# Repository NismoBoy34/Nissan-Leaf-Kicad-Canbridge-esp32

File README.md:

# Nissan-Leaf-Kicad-Canbridge-esp32
Esp32 based Can-bridge for the Nissan leaf / Env200 using more accessible components

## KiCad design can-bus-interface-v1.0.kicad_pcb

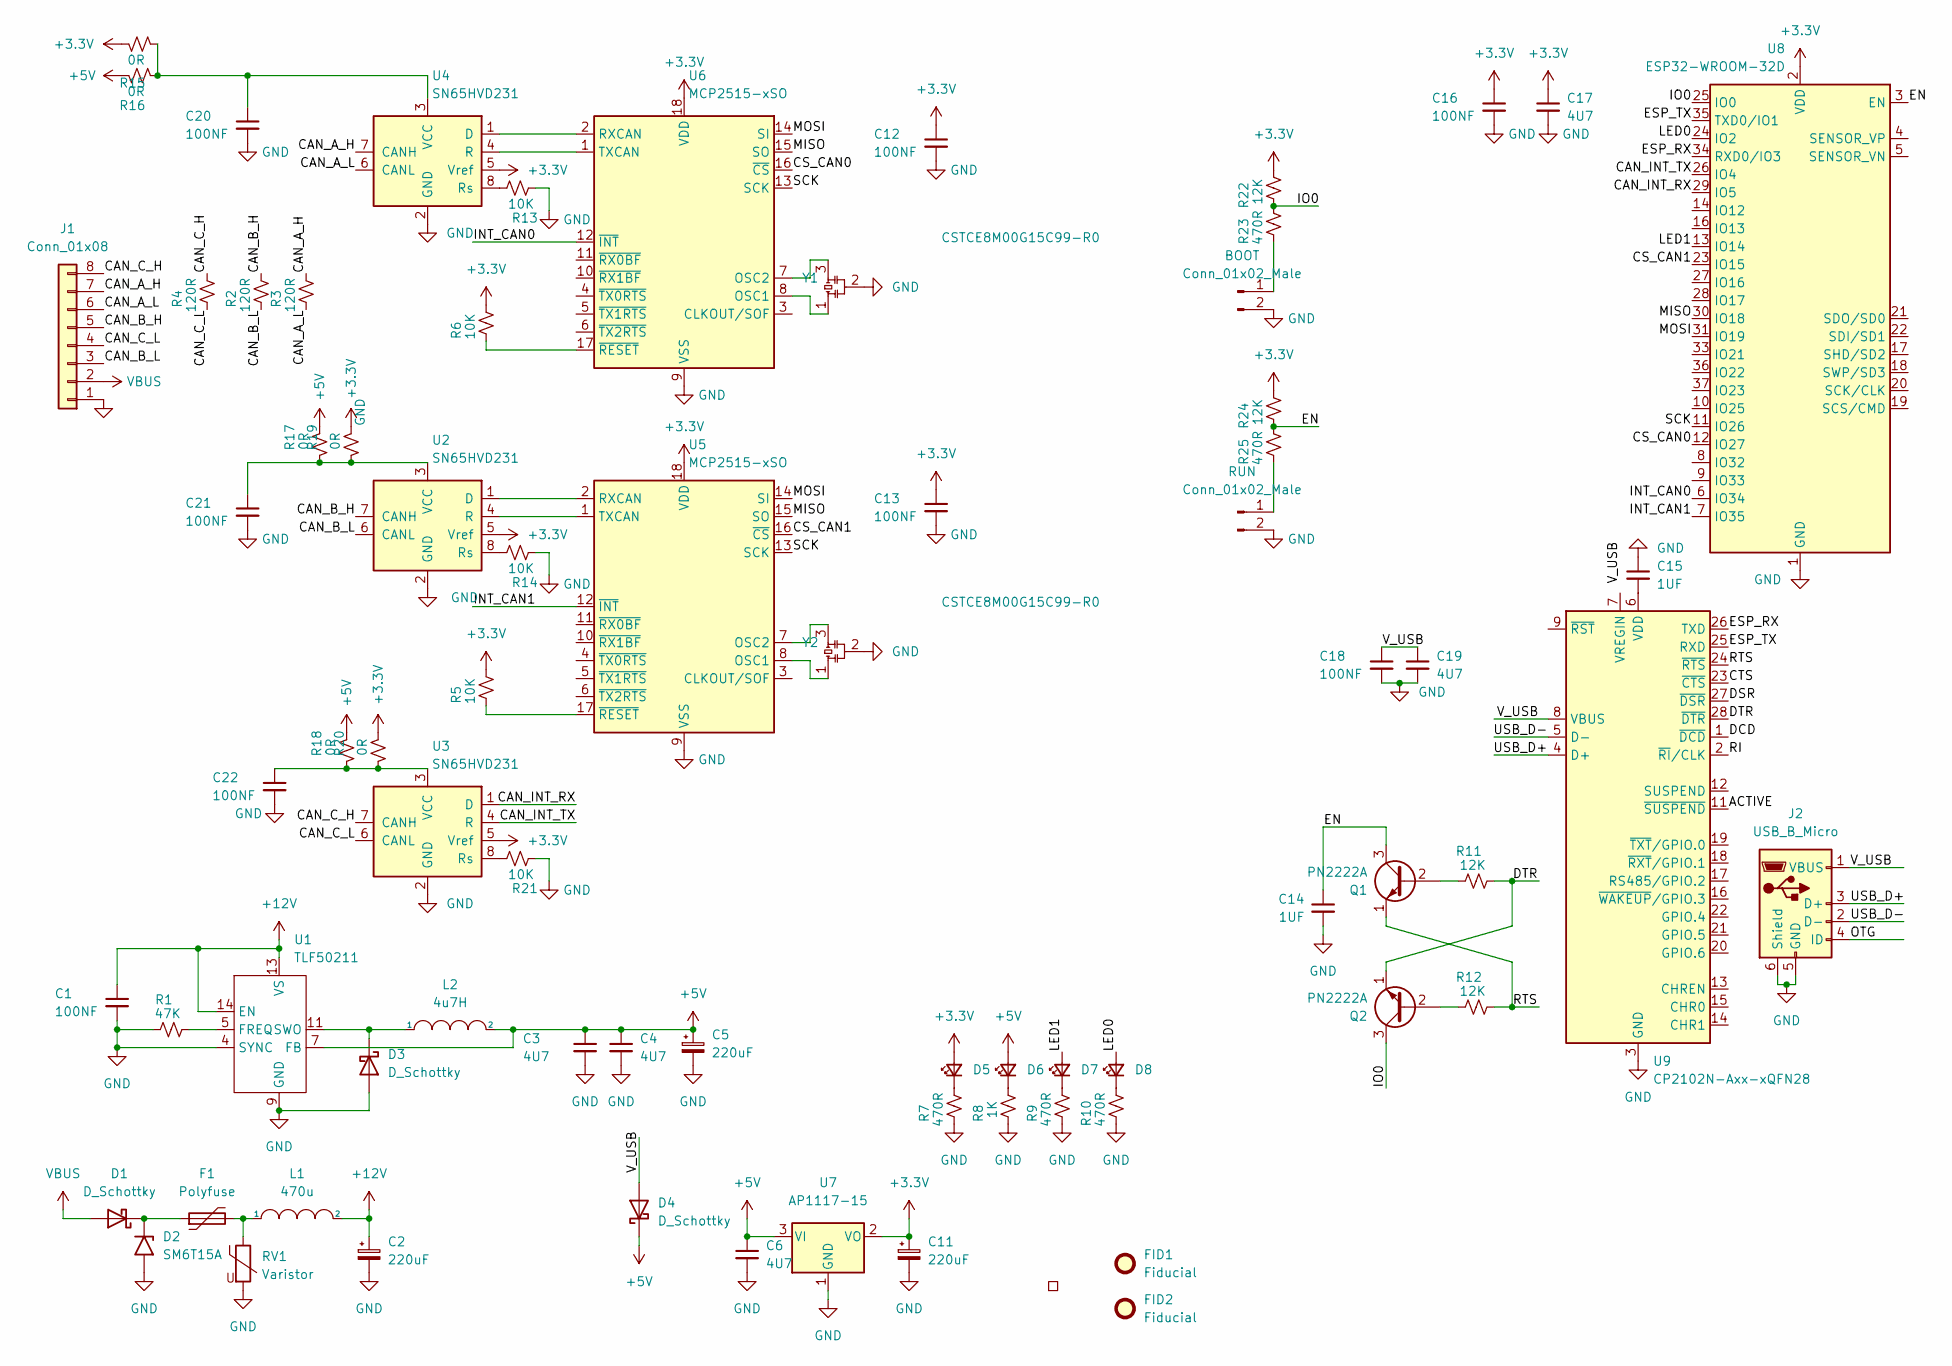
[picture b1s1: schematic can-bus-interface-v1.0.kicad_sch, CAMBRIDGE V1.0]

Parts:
*1: Signature
BOOT: Conn_01x02_Male; SolderJumper-2_P1.3mm_Open_Pad1.0x1.5mm
C1, C12, C13, C16, C18, C20, C21, C22: 100NF; C_0603_1608Metric
C2, C5, C11: 220uF; C_Elec_8x6.2
C3, C4, C6, C17, C19: 4U7; C_1210_3225Metric
C14, C15: 1UF; C_0805_2012Metric
D1, D3: D_Schottky; D_SMB
D2: SM6T15A; D_SMB
D4: D_Schottky; D_SOD-123
D5, D6, D7, D8: LED_Small; LED_0603_1608Metric
F1: Polyfuse; Fuse_1206_3216Metric
FID1, FID2: Fiducial; Fiducial_1mm_Mask2mm
J1: Conn_01x08; Molex_Mini-Fit_Jr_5566-08A_2x04_P4.20mm_Vertical
J2: USB_B_Micro; USB_Micro-B_Molex-105017-0001
L1: 470u; L_Bourns_SRP5030T
L2: 4u7H; L_Bourns_SRP5030T
Q1, Q2: PN2222A; SOT-23
R1: 47K; R_0603_1608Metric
R2, R3, R4: 120R; R_0603_1608Metric
R5, R6, R13, R14, R21: 10K; R_0603_1608Metric
R7, R9, R10, R23, R25: 470R; R_0603_1608Metric
R8: 1K; R_0603_1608Metric
R11, R12, R22, R24: 12K; R_0603_1608Metric
R15, R16, R17, R18, R19, R20: 0R; SolderJumper-2_P1.3mm_Open_Pad1.0x1.5mm
RUN: Conn_01x02_Male; SolderJumper-2_P1.3mm_Open_Pad1.0x1.5mm
RV1: Varistor; R_0402_1005Metric
U1: TLF50211; HTSSOP-14-1EP_4.4x5mm_P0.65mm_EP3.4x5mm_Mask3x3.1mm_Thermal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
U2, U3, U4: SN65HVD231; SOIC-8_3.9x4.9mm_P1.27mm
U5, U6: MCP2515-xSO; SOIC-18W_7.5x11.6mm_P1.27mm
U7: AP1117-15; SOT-223-3_TabPin2
U8: ESP32-WROOM-32D; ESP32-WROOM-32
U9: CP2102N-Axx-xQFN28; QFN-28-1EP_5x5mm_P0.5mm_EP3.35x3.35mm
Y1, Y2: CSTCE8M00G15C99-R0

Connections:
+3V3: C11.1, C12.1, C13.1, C16.1, C17.1, D5.2 (A), R5.2, R6.2, R15.1, R19.1, R20.1, R22.2, R24.2, U2.5 (Vref), U3.5 (Vref), U4.5 (Vref), U5.18 (VDD), U6.18 (VDD), U7.2 (VO), U8.2 (VDD)
+5V: C3.1, C4.1, C5.1, C6.1, D4.1 (K), D6.2 (A), L2.2, R16.1, R17.1, R18.1, U1.7 (FB), U7.3 (VI)
+12V: C1.1, C2.1, L1.2, U1.13 (VS), U1.14 (EN)
/ACTIVE: U9.11 (~SUSPEND)
/CAN_A_H: J1.7, R3.2, U4.7 (CANH)
/CAN_A_L: J1.6, R3.1, U4.6 (CANL)
/CAN_B_H: J1.5, R2.2, U2.7 (CANH)
/CAN_B_L: J1.3, R2.1, U2.6 (CANL)
/CAN_C_H: J1.8, R4.2, U3.7 (CANH)
/CAN_C_L: J1.4, R4.1, U3.6 (CANL)
/CAN_INT_RX: U3.1 (D), U8.29 (IO5)
/CAN_INT_TX: U3.4 (R), U8.26 (IO4)
/CS_CAN0: U6.16 (~CS), U8.12 (IO27)
/CS_CAN1: U5.16 (~CS), U8.23 (IO15)
/CTS: U9.23 (~CTS)
/DCD: U9.1 (~DCD)
/DSR: U9.27 (~DSR)
/DTR: Q2.1 (E), R11.2, U9.28 (~DTR)
/EN: C14.1, Q1.3 (C), R24.1, R25.2, U8.3 (EN)
/ESP_RX: U8.34 (RXD0/IO3), U9.26 (TXD)
/ESP_TX: U8.35 (TXD0/IO1), U9.25 (RXD)
/INT_CAN0: U6.12 (~INT), U8.6 (IO34)
/INT_CAN1: U5.12 (~INT), U8.7 (IO35)
/IO0: Q2.3 (C), R22.1, R23.2, U8.25 (IO0)
/LED0: D8.2 (A), U8.24 (IO2)
/LED1: D7.2 (A), U8.13 (IO14)
/MISO: U5.15 (SO), U6.15 (SO), U8.30 (IO18)
/MOSI: U5.14 (SI), U6.14 (SI), U8.31 (IO19)
/OTG: J2.4 (ID)
/RI: U9.2 (~RI/CLK)
/RTS: Q1.1 (E), R12.2, U9.24 (~RTS)
/SCK: U5.13 (SCK), U6.13 (SCK), U8.11 (IO26)
/USB_D+: J2.3 (D+), U9.4 (D+)
/USB_D-: J2.2 (D-), U9.5 (D-)
/V_USB: C18.1, C19.1, D4.2 (A), J2.1 (VBUS), U9.8 (VBUS)
GND: BOOT.2, C1.2, C2.2, C3.2, C4.2, C5.2, C6.2, C11.2, C12.2, C13.2, C14.2, C15.1, C16.2, C17.2, C18.2, C19.2, C20.2, C21.2, C22.2, D2.2 (A2), D3.2 (A), J1.1, J2.5 (GND), J2.6 (Shield), R1.1, R7.1, R8.1, R9.1, R10.1, R13.1, R14.1, R21.1, RUN.2, RV1.2, U1.4 (SYNC), U1.9 (GND), U1.10 (GND), U1.15 (GND), U2.2 (GND), U3.2 (GND), U4.2 (GND), U5.9 (VSS), U6.9 (VSS), U7.1 (GND), U8.1 (GND), U8.15 (GND), U8.38 (GND), U8.39 (GND), U9.3 (GND), U9.29 (GND), Y1.2, Y2.2
unnamed: C15.2, U9.6 (VDD)
unnamed: C20.1, R15.2, R16.2, U4.3 (VCC)
unnamed: C21.1, R17.2, R19.2, U2.3 (VCC)
unnamed: C22.1, R18.2, R20.2, U3.3 (VCC)
unnamed: D1.1 (K), D2.1 (A1), F1.1
unnamed: D3.1 (K), L2.1, U1.11 (SWO)
unnamed: D5.1 (K), R7.2
unnamed: D6.1 (K), R8.2
unnamed: D7.1 (K), R9.2
unnamed: D8.1 (K), R10.2
unnamed: F1.2, L1.1, RV1.1
unnamed: BOOT.1, R23.1
unnamed: R25.1, RUN.1
unnamed: Q1.2 (B), R11.1
unnamed: Q2.2 (B), R12.1
unnamed: R1.2, U1.5 (FREQ)
unnamed: R5.1, U5.17 (~RESET)
unnamed: R6.1, U6.17 (~RESET)
unnamed: R13.2, U4.8 (Rs)
unnamed: R14.2, U2.8 (Rs)
unnamed: R21.2, U3.8 (Rs)
unnamed: U2.1 (D), U5.2 (RXCAN)
unnamed: U2.4 (R), U5.1 (TXCAN)
unnamed: U4.1 (D), U6.2 (RXCAN)
unnamed: U4.4 (R), U6.1 (TXCAN)
unnamed: U5.7 (OSC2), Y2.3
unnamed: U5.8 (OSC1), Y2.1
unnamed: U6.7 (OSC2), Y1.3
unnamed: U6.8 (OSC1), Y1.1
VBUS: D1.2 (A), J1.2

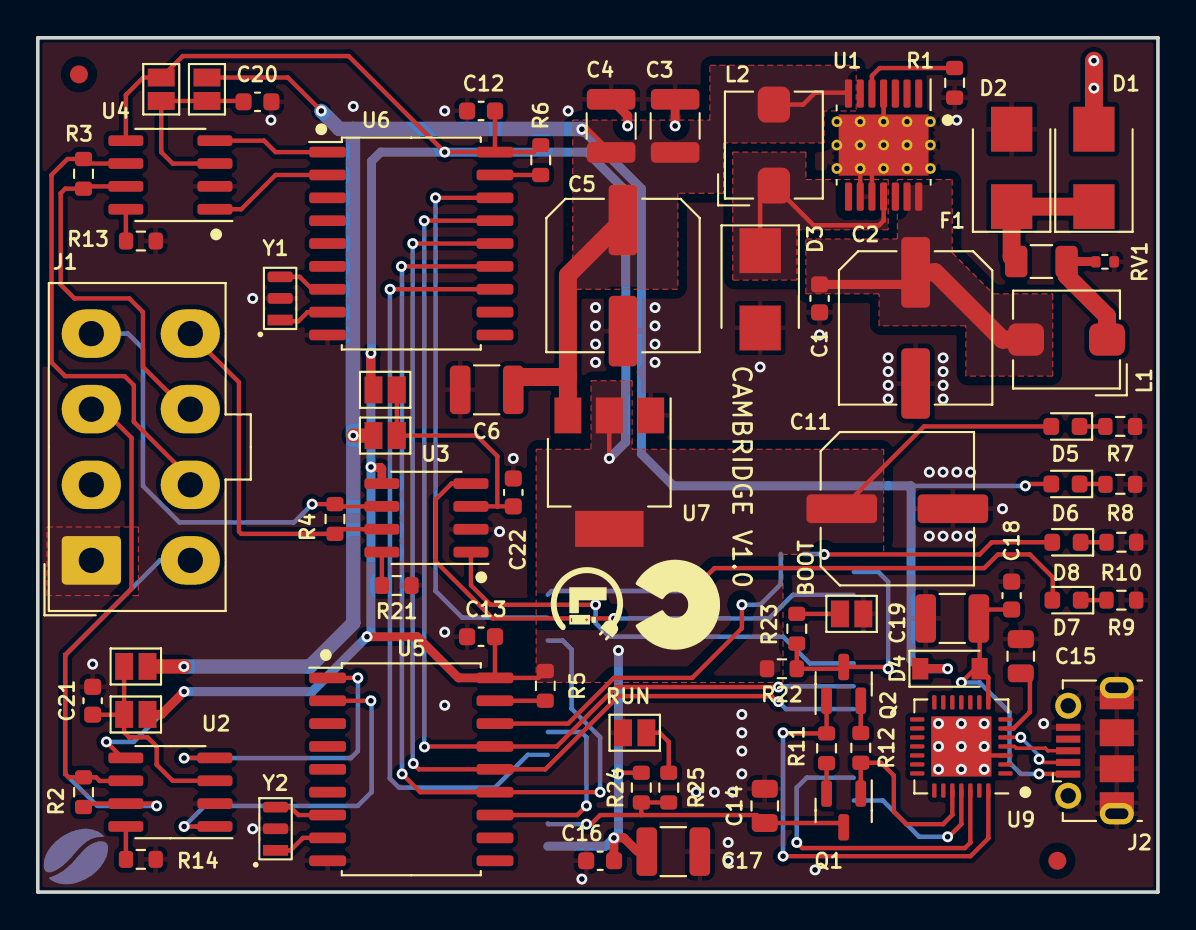
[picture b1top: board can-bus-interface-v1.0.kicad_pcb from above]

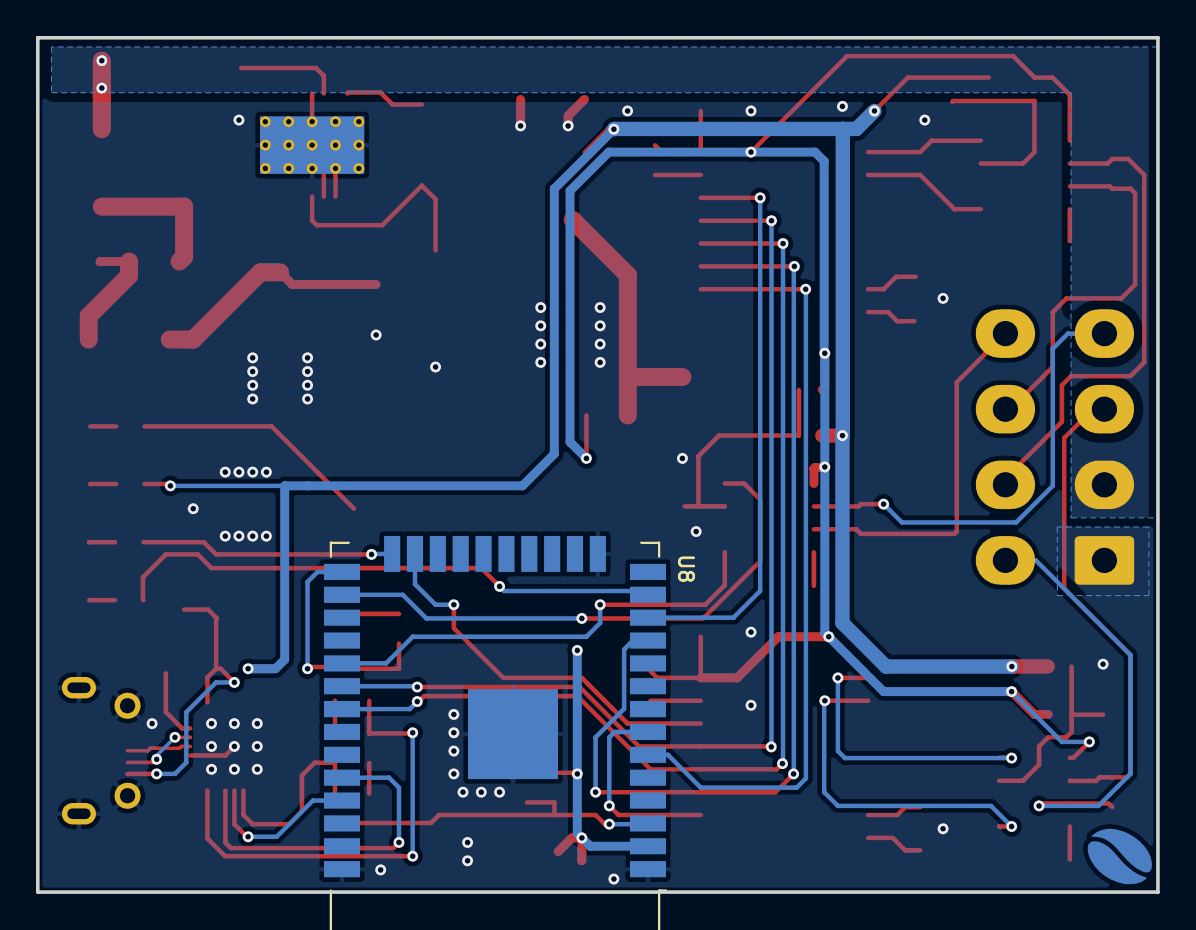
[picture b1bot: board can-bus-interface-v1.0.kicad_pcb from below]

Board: 2 copper layers, 62.2 x 47.5 mm, 75 parts (2 on the bottom side), 60 nets.
